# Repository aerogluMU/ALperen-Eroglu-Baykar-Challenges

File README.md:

# Alperen-Eroglu-Baykar-Challenge
## Challenge 1
- By using **Thread**, the LEDs are made to blink at intervals of seconds as the **"shutter_period_time"** value in the config.json file.
- Added button **interrupt** and when the interrupt is triggered, **timestamp** value is taken and this value is saved in ts_buffer array.
- By using **Thread**, the values in ts_buffer are saved to the **shutter.csv** file at intervals of seconds (if a button interrupt occurred) as much as the **"shutter_period_time"** value in the config.json file.
- Added **i2c_flag**. The flag is set after timestamps are recorded in the shutter.csv file. If i2c_flag is set, "hello" message is sent to **STM32F407VG** card from **i2c line** and wakes **Receive interrupt** on STM32F407VG card. Then, 4 bytes of data are taken from the STM32F407VG card and the **counter** number is printed by collecting this data.

### Cards Used
- Raspberry Pi 3B+
- STM32F407VG Disco

### Pinouts of Raspberry Pi 3B+

- Led 1 (RED) = 7
- Led 2 (Green) = 0
- Button = 2
- I2C SDA = 3
- I2C SCL = 5

> Mode of Leds --> Out
> Mode of Button --> In
> PUPD of Button --> Pull Up

### Pinouts of STM32F407VG Disco
- PB10 --> I2C2_SCL
- PB11 --> I2C2_SDA
> I2C2 is used for this project

### Config.json

    {"shutter_period_time":1}

### System Images

> [Click here for the video of the system in operation](https://s8.gifyu.com/images/ezgif-3-93caae81eb.gif)

### FlowChart of Raspberry Pi 3B+
```mermaid
graph  TD
    A[System Start]  -->B[Initialization]
    B  -->  C(Read shutter_period_time value in config.json)
    C  -->  T1[thread_shutter_pulse begin]
    C  -->  T2[thread_shutter_record begin]
    C  -->  INT[button_callback begin]
    C  -->  T3[thread_i2c begin]

    T1  -->  T11(Open LED1 and LED2)
    T11  -->  T1D1(Wait seconds at shutter_period_time)
    T1D1  -->  T12(Close LED1 and LED2)
    T12  -->  T1D2(Wait seconds at shutter_period_time)
    T1D2  -->  T11

    T2  -->  T2INT{Is it_occured value set?}
    T2INT  -->  |Yes| T2SAVE(Save values from ts_buffer array to shutter.csv)
    T2SAVE  -->  T2CLEAR(Clear it_occured flag and ts_buffer array)
    T2CLEAR  -->  T2SET(Set i2c_flag)
    T2SET  -->  T2D1(Wait seconds at shutter_period_time)
    T2D1  -->  T2INT
    T2INT  -->  |No| T2D2(Wait seconds at shutter_period_time)
    T2D2  -->  T2INT

    INT  -->  INT_ISPRESSED{Is button pressed?}
    INT_ISPRESSED  -->  |Yes| INT_ISPRESSED_Y(Save current timestamp value to ts_buffer array and print it with cout)
    INT_ISPRESSED_Y  -->  INT_ISPRESSED_1(set it_occured flag)
    INT_ISPRESSED_1  -->  INT_ISPRESSED
    INT_ISPRESSED  -->  |No| INT_ISPRESSED

    T3  -->  T3_INT{Is i2c_flag set?}
    T3_INT  -->  |Yes| T3_STM(Wake Receive Interrupt on STM32F407VG board)
    T3_STM  -->  T3_CNT(Sum the incoming data bytes and print the sum which is the counter value)
    T3_CNT  -->  T3_RST(Reset i2c_flag)
    T3_RST  -->  T3_INT
    T3_INT  -->  |No| T3_INT
```

### FlowChart of STM32F407VG Disco

```mermaid
graph TD
    A[System Start] -->B[Initialization]
    B --> C(Set 0 all bytes of i2c_veri)
    C --> D{Is receive interrupt occured?}
    D --> |No| D
    D --> |Yes| E(Send 4 byte i2c_veri)
    
    E --> CFB{Is first byte of i2c_veri less then 255?}
    CFB --> |Yes| FBI(Increase first byte of i2c_veri)
    FBI --> D
    CFB --> |No| CSB{Is first byte of i2c_veri equal 255 and second byte of i2c_veri less then 255?}
    
    CSB --> |Yes| SBI(Increase second byte of i2c_veri)
    SBI --> D
    CSB --> |No| CTB{Is second byte of i2c_veri equal 255 and third byte of i2c_veri less then 255?}
    
    CTB --> |Yes| TBI(Increase third byte of i2c_veri)
    TBI --> D
    CTB --> |No| CFFB{Is third byte of i2c_veri equal 255 and fourth byte of i2c_veri less then 255?}
    
    CFFB --> |Yes| FFBI(Increase fourth byte of i2c_veri)
    FFBI --> D
    CFFB --> |No| RST(Reset i2c_veri array)
    RST --> D
```

## Challenge 2

- Added 9 pin header for SD card connections from camera.
- Added SD card socket to save data from camera to SD card.
- Added GL827L integrated circuit and USB socket to transfer the data from the camera to the computer.
- 74LVC1G18 demultiplexers have been added to transfer the data from the camera to SD card or USB on demand.

### 74LVC1G18 Work Structure

> A --> Camera Pins
> S --> MCU Selection
> 1Y --> SD Card
> 2Y --> SD Card Reader (USB)

As we can see from the table, if the selective value from the MCU pin **is equal to 0**, the data from the camera will be transferred to the **SD card**, if it **is equal to 1**, the data from the camera will be transferred to the **USB**.

### Schematic

### PCB

### 3D PCB

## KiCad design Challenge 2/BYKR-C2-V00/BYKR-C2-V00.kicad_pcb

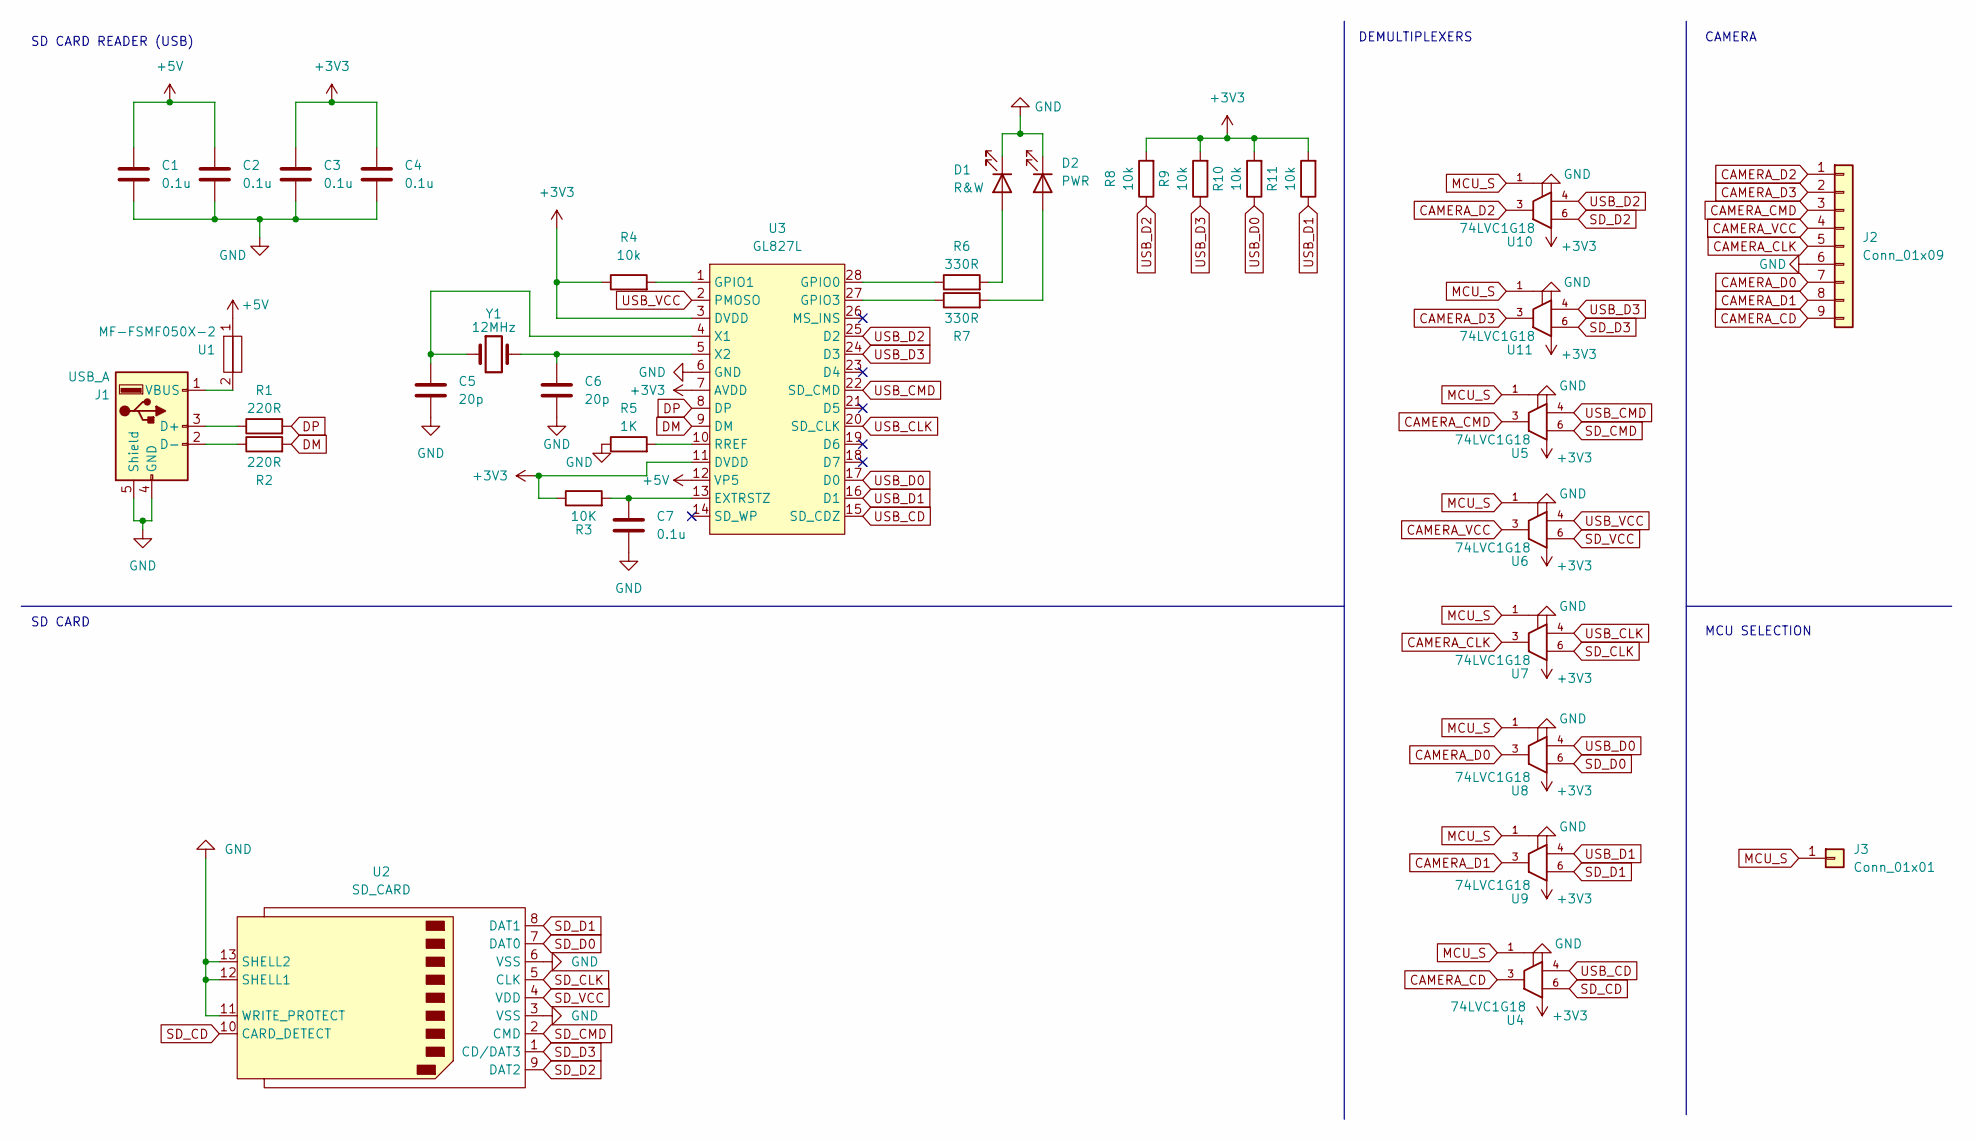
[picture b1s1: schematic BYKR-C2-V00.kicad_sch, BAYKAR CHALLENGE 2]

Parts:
C1, C2, C3, C4, C7: 0.1u; C_0805_2012Metric
C5, C6: 20p; C_0805_2012Metric
D1: R&W; LED_1206_3216Metric
D2: PWR; LED_1206_3216Metric
J1: USB_A; USB
J2: Conn_01x09; PinHeader_1x09_P2.54mm_Vertical
J3: Conn_01x01; PinHeader_1x01_P2.54mm_Vertical
R1, R2: 220R; R_0805_2012Metric
R3: 10K; R_0805_2012Metric
R4, R8, R9, R10, R11: 10k; R_0805_2012Metric
R5: 1K; R_0805_2012Metric
R6, R7: 330R; R_0805_2012Metric
U1: MF-FSMF050X-2; R_0805_2012Metric
U2: SD_CARD; BYKR_SD
U3: GL827L; SSOP28
U4, U5, U6, U7, U8, U9, U10, U11: 74LVC1G18; SOT-363_SC-70-6
Y1: 12MHz; Crystal_SMD_MicroCrystal_CC8V-T1A-2Pin_2.0x1.2mm_HandSolder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

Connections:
+3V3: C3.1, C4.1, R3.1, R4.1, R8.2, R9.2, R10.2, R11.2, U3.3 (DVDD), U3.7 (AVDD), U3.11 (DVDD), U4.5 (VCC), U5.5 (VCC), U6.5 (VCC), U7.5 (VCC), U8.5 (VCC), U9.5 (VCC), U10.5 (VCC), U11.5 (VCC)
+5V: C1.1, C2.1, U1.1, U3.12 (VP5)
CAMERA_CD: J2.9, U4.3
CAMERA_CLK: J2.5, U7.3
CAMERA_CMD: J2.3, U5.3
CAMERA_D0: J2.7, U8.3
CAMERA_D1: J2.8, U9.3
CAMERA_D2: J2.1, U10.3
CAMERA_D3: J2.2, U11.3
CAMERA_VCC: J2.4, U6.3
DM: R2.2, U3.9 (DM)
DP: R1.2, U3.8 (DP)
GND: C1.2, C2.2, C3.2, C4.2, C5.2, C6.2, C7.2, D1.1 (K), D2.1 (K), J1.4 (GND), J1.5 (Shield), J2.6, R5.1, U2.3 (VSS), U2.6 (VSS), U2.11 (WRITE_PROTECT), U2.12 (SHELL1), U2.13 (SHELL2), U3.6 (GND), U4.2 (GND), U5.2 (GND), U6.2 (GND), U7.2 (GND), U8.2 (GND), U9.2 (GND), U10.2 (GND), U11.2 (GND)
MCU_S: J3.1, U4.1, U5.1, U6.1, U7.1, U8.1, U9.1, U10.1, U11.1
unnamed: C5.1, U3.4 (X1), Y1.1
unnamed: C6.1, U3.5 (X2), Y1.2
unnamed: C7.1, R3.2, U3.13 (EXTRSTZ)
unnamed: D1.2 (A), R6.2
unnamed: D2.2 (A), R7.2
unnamed: J1.1 (VBUS), U1.2
unnamed: J1.2 (D-), R2.1
unnamed: J1.3 (D+), R1.1
unnamed: R4.2, U3.1 (GPIO1)
unnamed: R5.2, U3.10 (RREF)
unnamed: R6.1, U3.28 (GPIO0)
unnamed: R7.1, U3.27 (GPIO3)
SD_CD: U2.10 (CARD_DETECT), U4.6
SD_CLK: U2.5 (CLK), U7.6
SD_CMD: U2.2 (CMD), U5.6
SD_D0: U2.7 (DAT0), U8.6
SD_D1: U2.8 (DAT1), U9.6
SD_D2: U2.9 (DAT2), U10.6
SD_D3: U2.1 (CD/DAT3), U11.6
SD_VCC: U2.4 (VDD), U6.6
USB_CD: U3.15 (SD_CDZ), U4.4
USB_CLK: U3.20 (SD_CLK), U7.4
USB_CMD: U3.22 (SD_CMD), U5.4
USB_D0: R10.1, U3.17 (D0), U8.4
USB_D1: R11.1, U3.16 (D1), U9.4
USB_D2: R8.1, U3.25 (D2), U10.4
USB_D3: R9.1, U3.24 (D3), U11.4
USB_VCC: U3.2 (PMOSO), U6.4

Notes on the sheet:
SD CARD READER (USB)
CAMERA
DEMULTIPLEXERS
SD CARD
MCU SELECTION

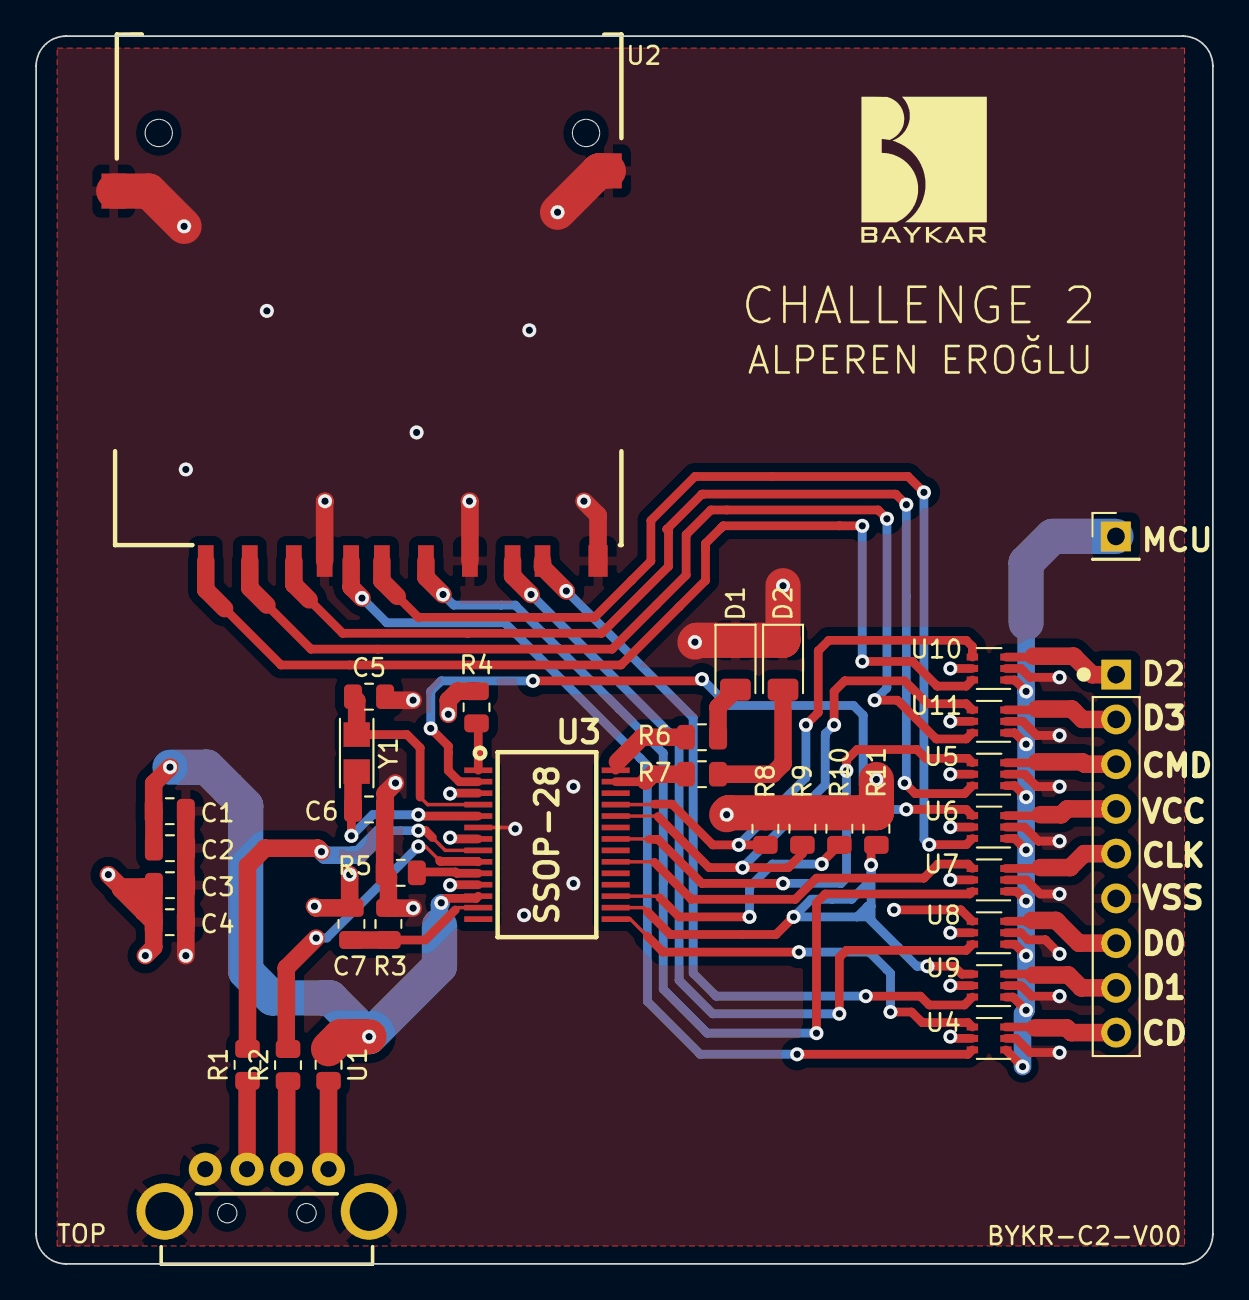
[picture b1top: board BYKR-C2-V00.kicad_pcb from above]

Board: 4 copper layers, 66.8 x 69.7 mm, 35 parts (0 on the bottom side), 42 nets.

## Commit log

2022-06-03 Added Challenge 1 and 2
2022-06-03 Updated System Gif
2022-06-05 Added I2C Communication
2022-06-05 STM32F407VG I2C Communication
2022-06-05 Added I2C and STM32F407VG Information
2022-06-06 Fixed FlowCharts Error
2022-06-06 Updated FlowChart
2022-06-06 Updated FlowCharts
2022-06-06 Updated I2C Communication
